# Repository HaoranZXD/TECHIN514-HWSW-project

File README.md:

# "AtmosTrack" Personal Weather Station

## Overview

"AtmosTrack" provides localized weather monitoring by collecting atmospheric data in real-time. It's designed for domestic use, featuring an outdoor sensor unit that is compact and waterproof. The indoor display boasts an intuitive gauge and vibrant LED indicators, all encapsulated within a modern design.

## Sensing Device - "AtmosSensor"

The "AtmosSensor" outdoor unit is outfitted with the HTU21D sensor for accurate humidity and temperature measurements, alongside the CCS811 sensor for CO2 and VOC levels. These are managed by the ESP32 processor. Data is wirelessly transmitted to the indoor unit via Wi-Fi. The unit is powered by a LP323450 rechargeable lithium polymer ion battery pack, ensuring continuous operation.

## Display Device - "AtmosDisplay"

The indoor "AtmosDisplay" presents the weather data on a ST7735R TFT LCD and utilizes a custom gauge with a stepper motor (28BYJ-48) for an analog display. It's powered by an ESP32 processor, featuring Wi-Fi connectivity for real-time data updates. User interaction is facilitated through a capacitive touch button (TTP223). The display unit is powered by a 18650 lithium-ion battery, providing portability and easy recharging.

## Communication and System Diagrams

The "AtmosSensor" and "AtmosDisplay" units communicate wirelessly through Wi-Fi, ensuring a consistent stream of data. The ESP32 of "AtmosSensor" is responsible for gathering sensor data and performing initial processing before transmission. The ESP32 of "AtmosDisplay" processes the data upon receipt and updates the display accordingly, offering a dynamic and interactive way to visualize weather data.

## Datasheets Folder

- `[HTU21D](datasheets/HTU21D.pdf)`
- `[CCS811](datasheets/CCS811.pdf)`
- `[ESP32](datasheets/ESP32-S3.pdf)`
- `[28BYJ-48](datasheets/28BYJ-48.pdf)`
- `[ST7735R](datasheets/ST7735R.pdf)`
- `[TTP223](datasheets/TTP223.pdf)`
- `[ICR18650](datasheets/ICR18650.pdf)`
- `[LP323450](datasheets/LP323450.pdf)`

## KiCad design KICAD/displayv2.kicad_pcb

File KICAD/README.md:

This is a folder for KICAD project

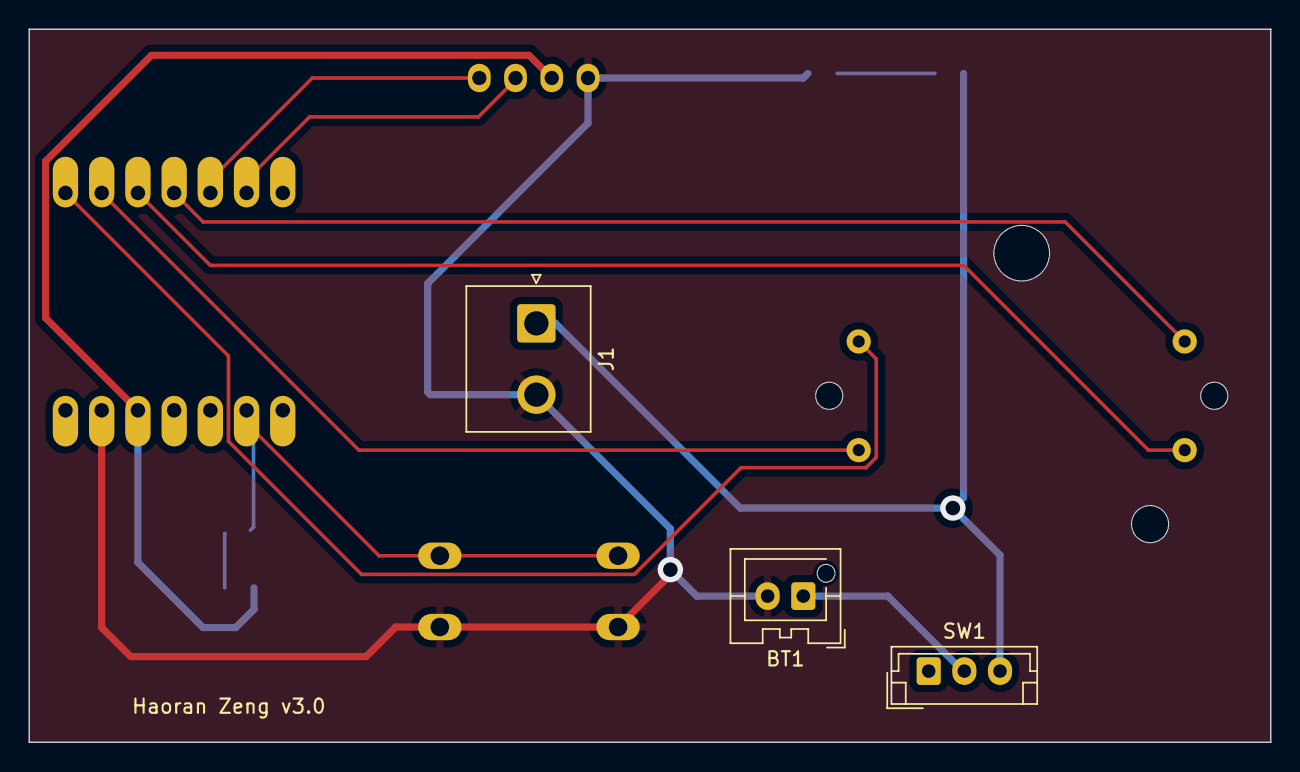
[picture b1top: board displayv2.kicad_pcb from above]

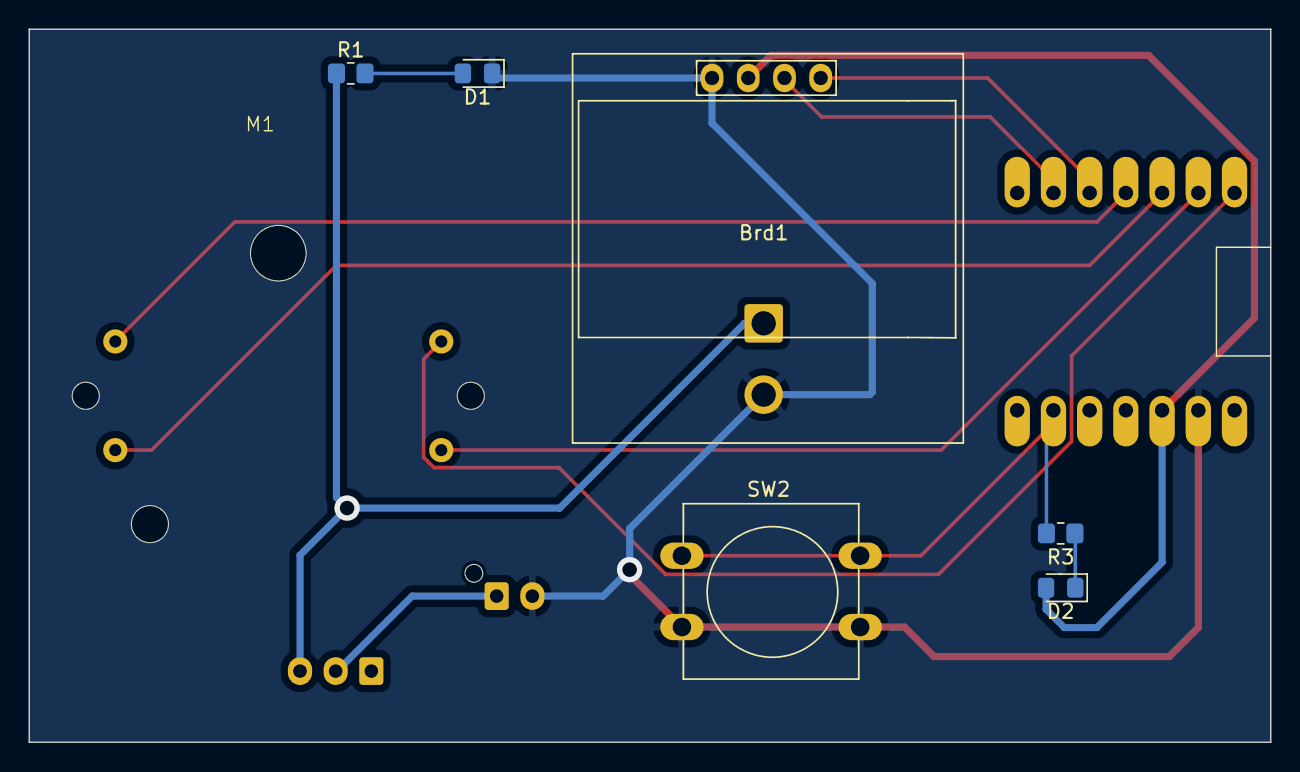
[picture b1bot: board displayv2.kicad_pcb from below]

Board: 2 copper layers, 87.1 x 50.0 mm, 11 parts (8 on the bottom side), 13 nets.

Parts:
BT1: Battery_Cell; JST_XA_B02B-XASK-1-A_1x02_P2.50mm_Vertical
Brd1: SSD1306; 128x64OLED
D1, D2: LED; LED_0805_2012Metric_Pad1.15x1.40mm_HandSolder
J1: Conn_01x02_Pin; JST_NV_B02P-NV_1x02_P5.00mm_Vertical
M1: Stepper_Motor_bipolar; x27_stepper
R1: 85Ω; R_0805_2012Metric_Pad1.20x1.40mm_HandSolder
R3: 65Ω; R_0805_2012Metric_Pad1.20x1.40mm_HandSolder
SW1: SW_SPDT; JST_EH_B3B-EH-A_1x03_P2.50mm_Vertical
SW2: SW_SPST; SW_PUSH-12mm
U1: XIAO_ESP32_SENSE

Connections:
/3V3: Brd1.2 (VCC), D2.2 (A), U1.10 (3V3)
/BAT: BT1.1 (+), SW1.2 (B)
/BTN: R3.2, SW2.1 (A), U1.13 (GPIO7_A8_D8_SCK)
/MOTOR1: M1.1, U1.1 (GPIO1_A0_D0)
/MOTOR2: M1.2 (-), U1.2 (GPIO2_A1_D1)
/MOTOR3: M1.3, U1.3 (GPIO3_A2_D2)
/MOTOR4: M1.4, U1.4 (GPIO4_A3_D3)
/SCL: Brd1.3 (SCL), U1.6 (GPIO6_A5_D5_SCL)
/SDA: Brd1.4 (SDA), U1.5 (GPIO4_A3_D3_SDA)
/VCC: J1.1, R1.1, SW1.3 (C)
GND: BT1.2 (-), Brd1.1 (GND), D1.1 (K), J1.2, SW2.2 (B), U1.9 (GND)
unnamed: D1.2 (A), R1.2
unnamed: D2.1 (K), R3.1

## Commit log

2024-01-17 README and datasheets added
2024-01-17 slides added
2024-01-18 Add first version of sch and pcb
2024-02-06 update datasheets
2024-02-06 Add a simple power mode spreadsheet
2024-02-21 init
2024-03-05 updated code
2024-03-06 final version of kicad
